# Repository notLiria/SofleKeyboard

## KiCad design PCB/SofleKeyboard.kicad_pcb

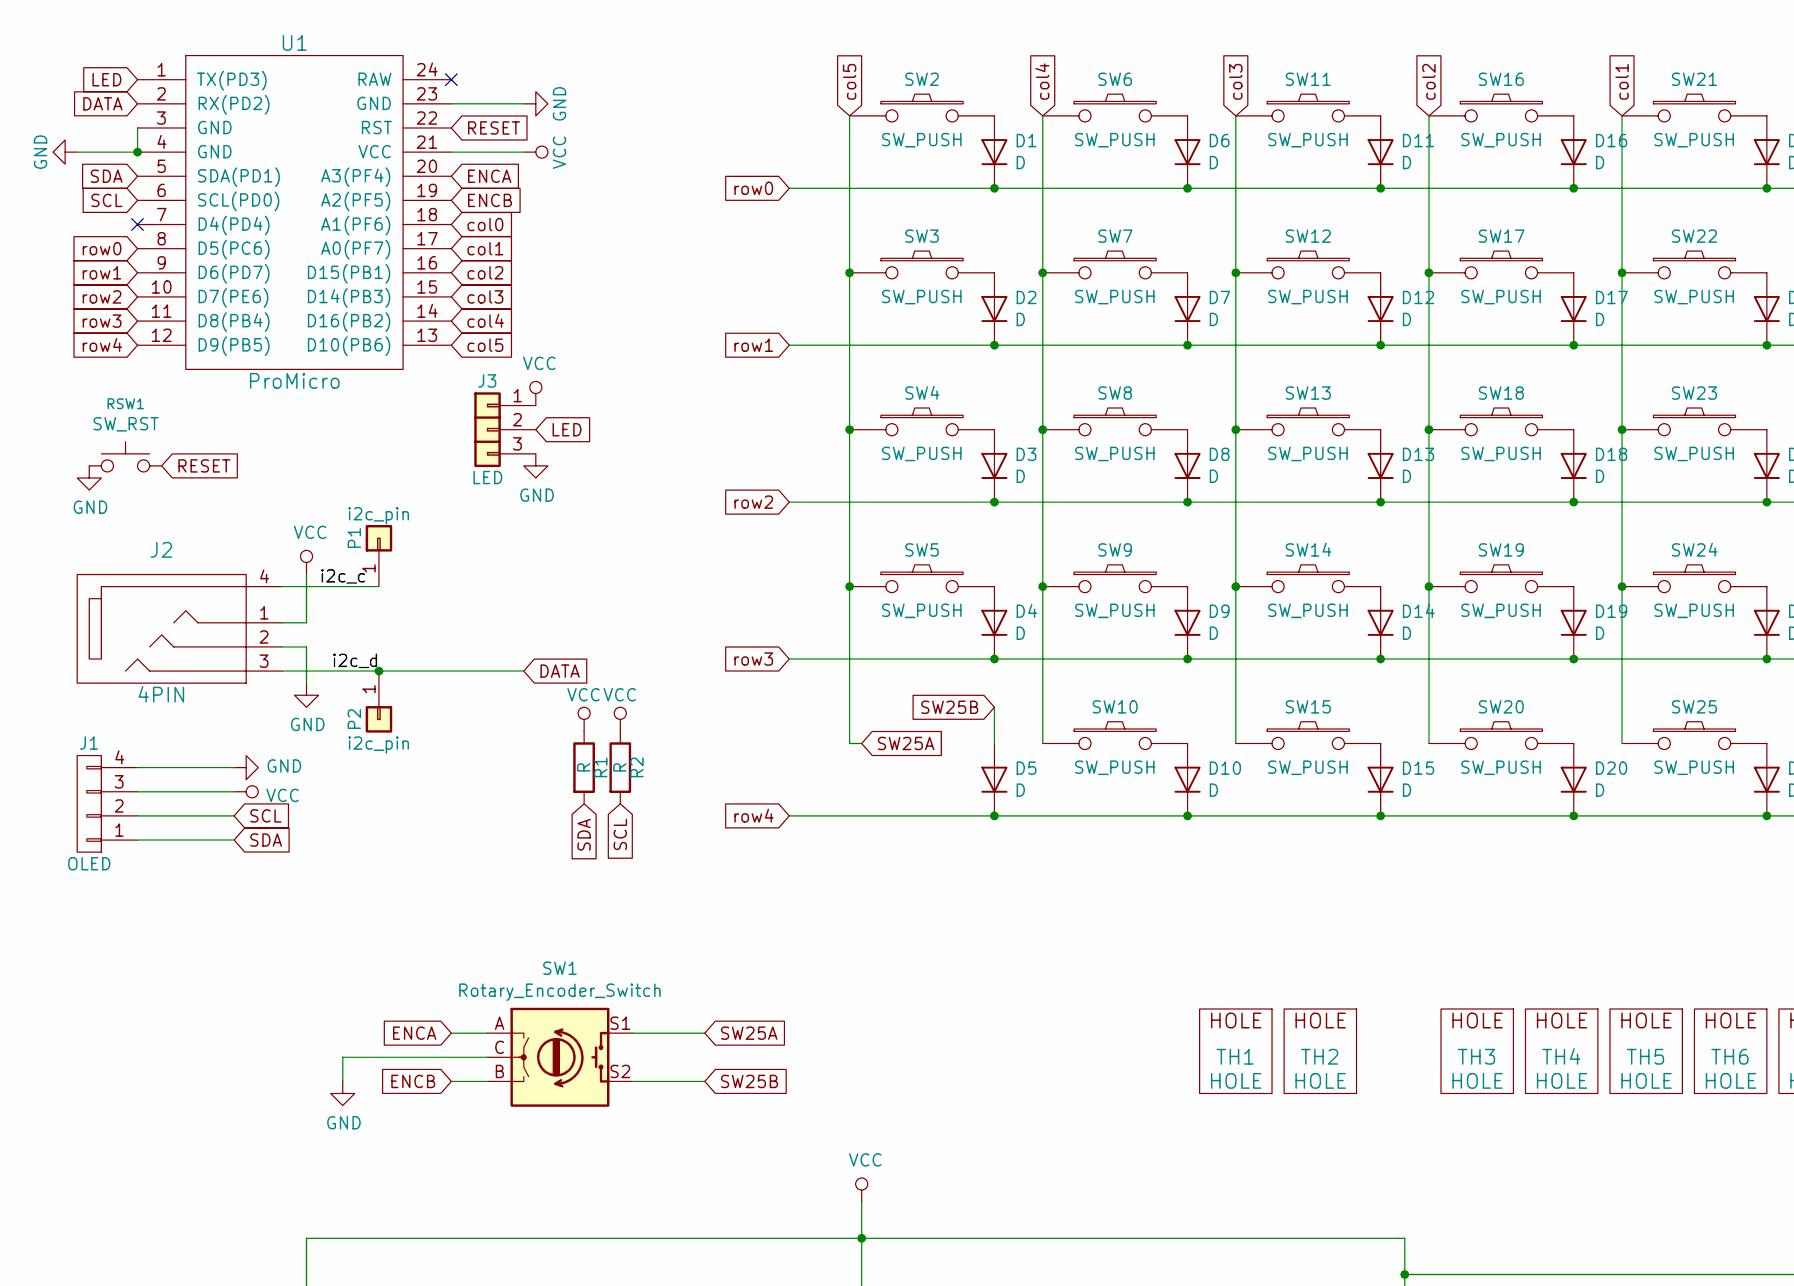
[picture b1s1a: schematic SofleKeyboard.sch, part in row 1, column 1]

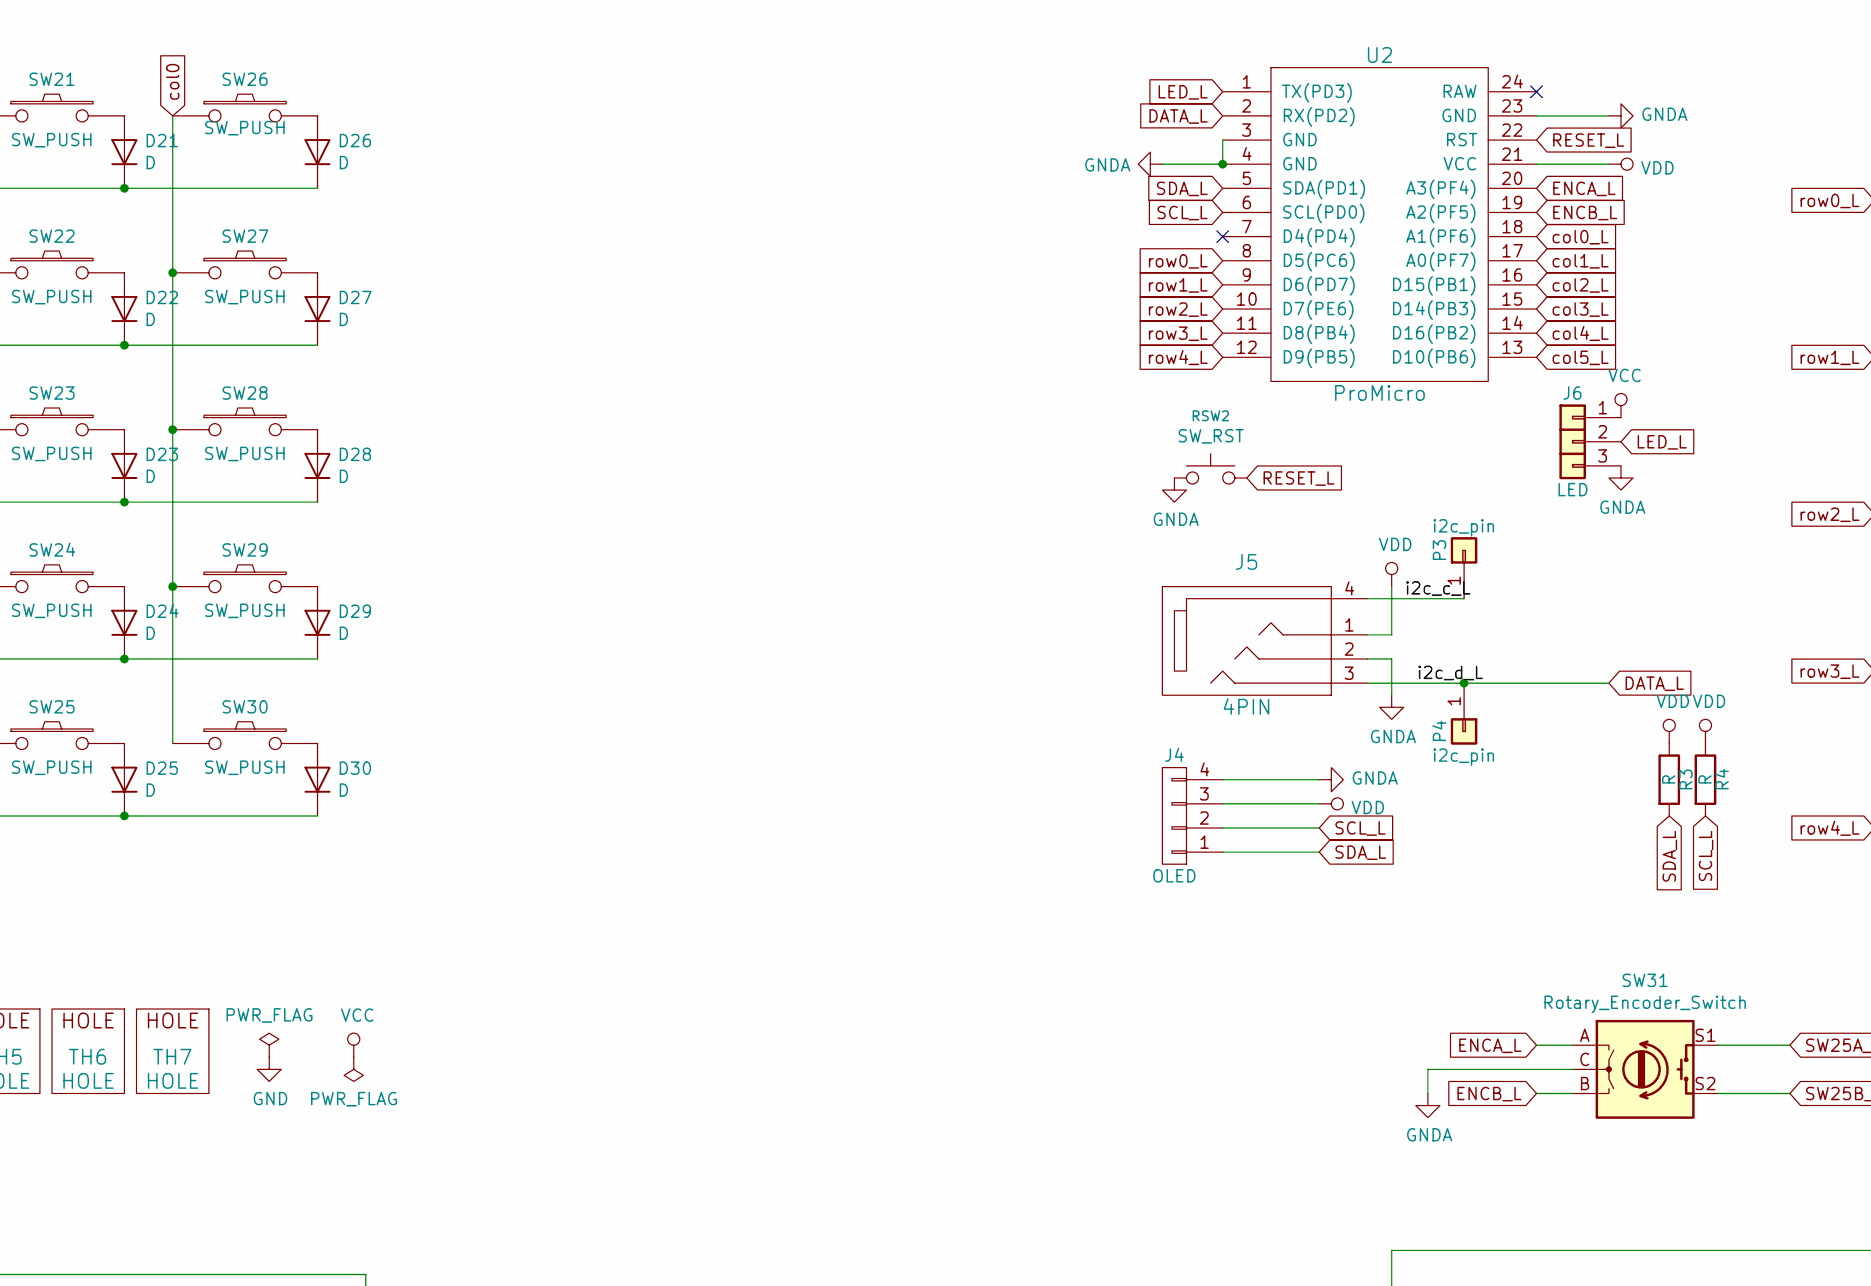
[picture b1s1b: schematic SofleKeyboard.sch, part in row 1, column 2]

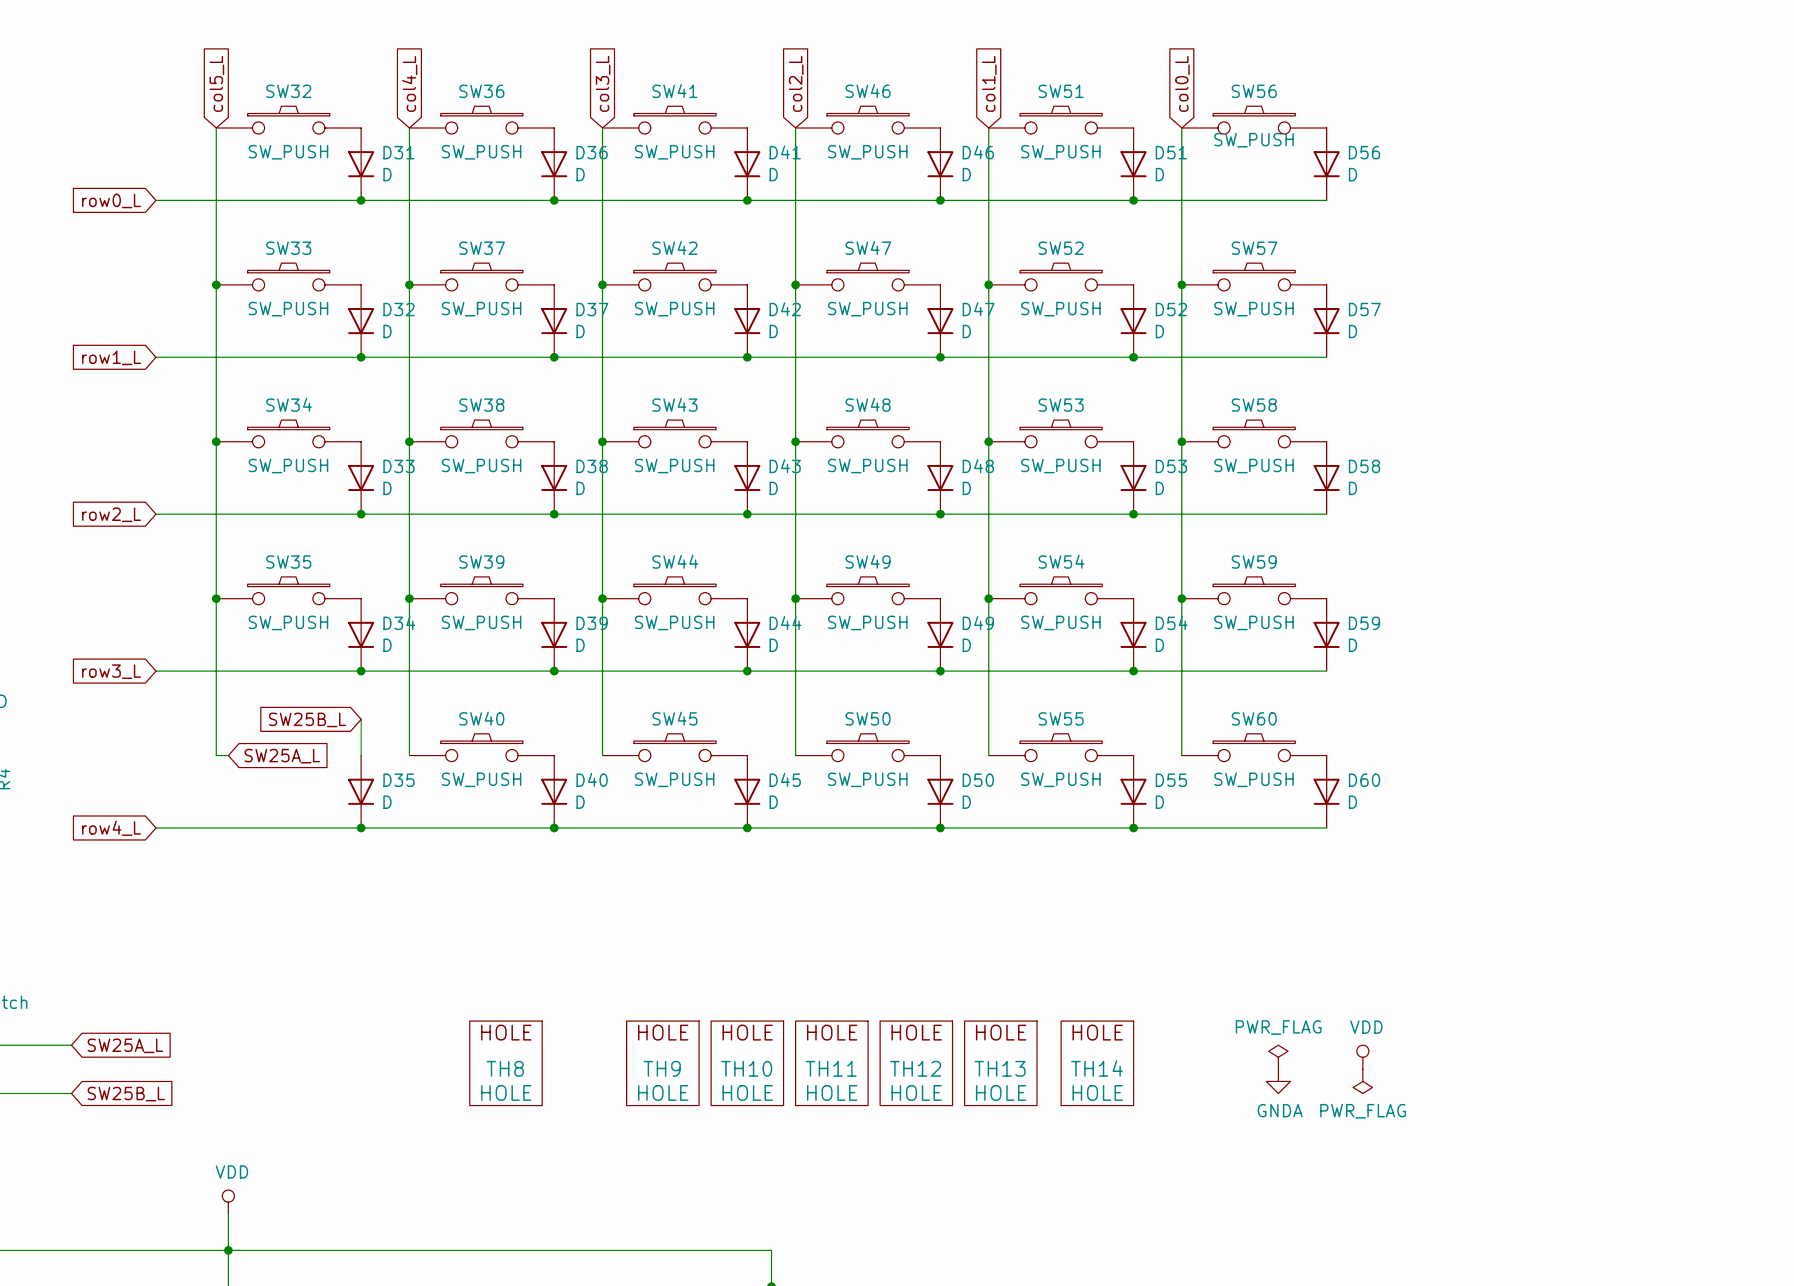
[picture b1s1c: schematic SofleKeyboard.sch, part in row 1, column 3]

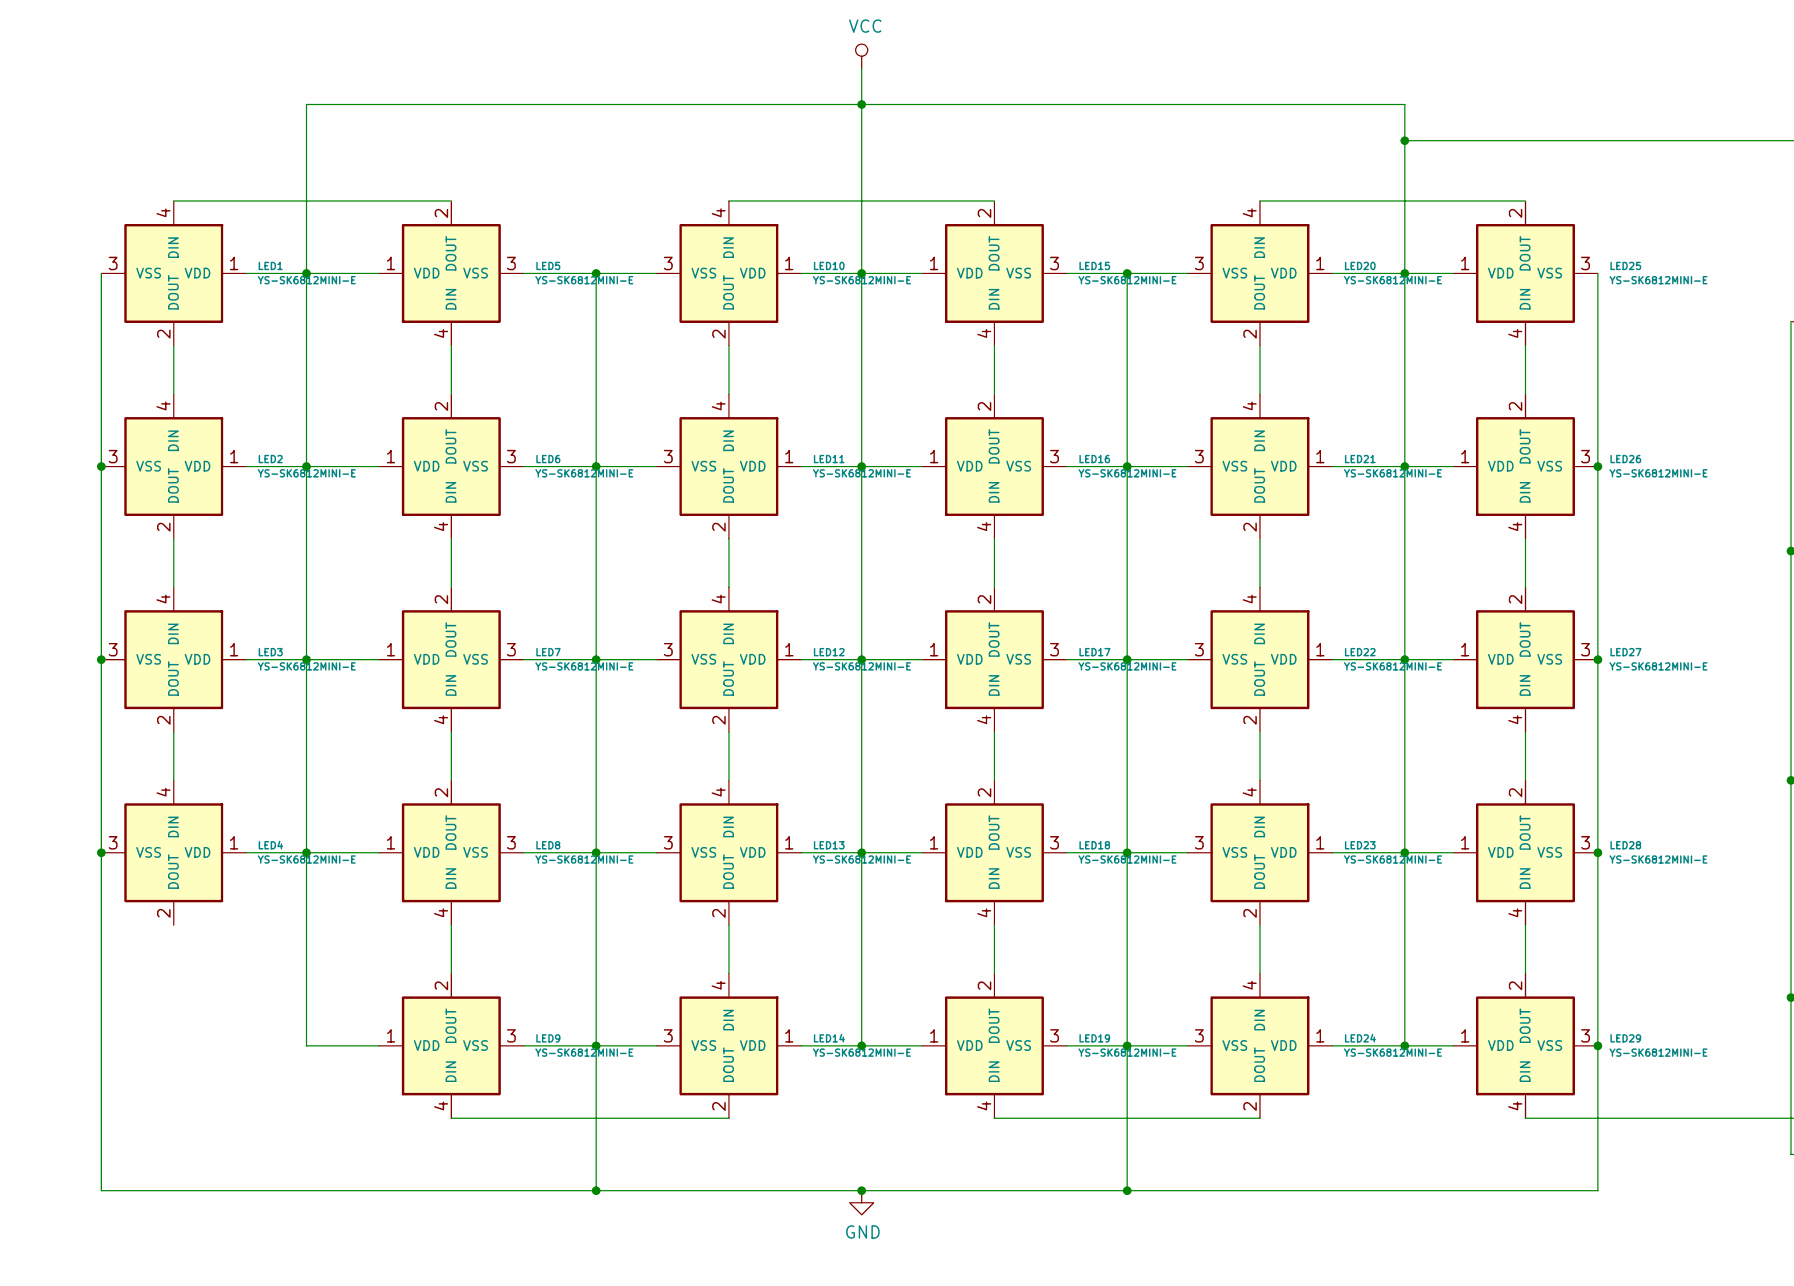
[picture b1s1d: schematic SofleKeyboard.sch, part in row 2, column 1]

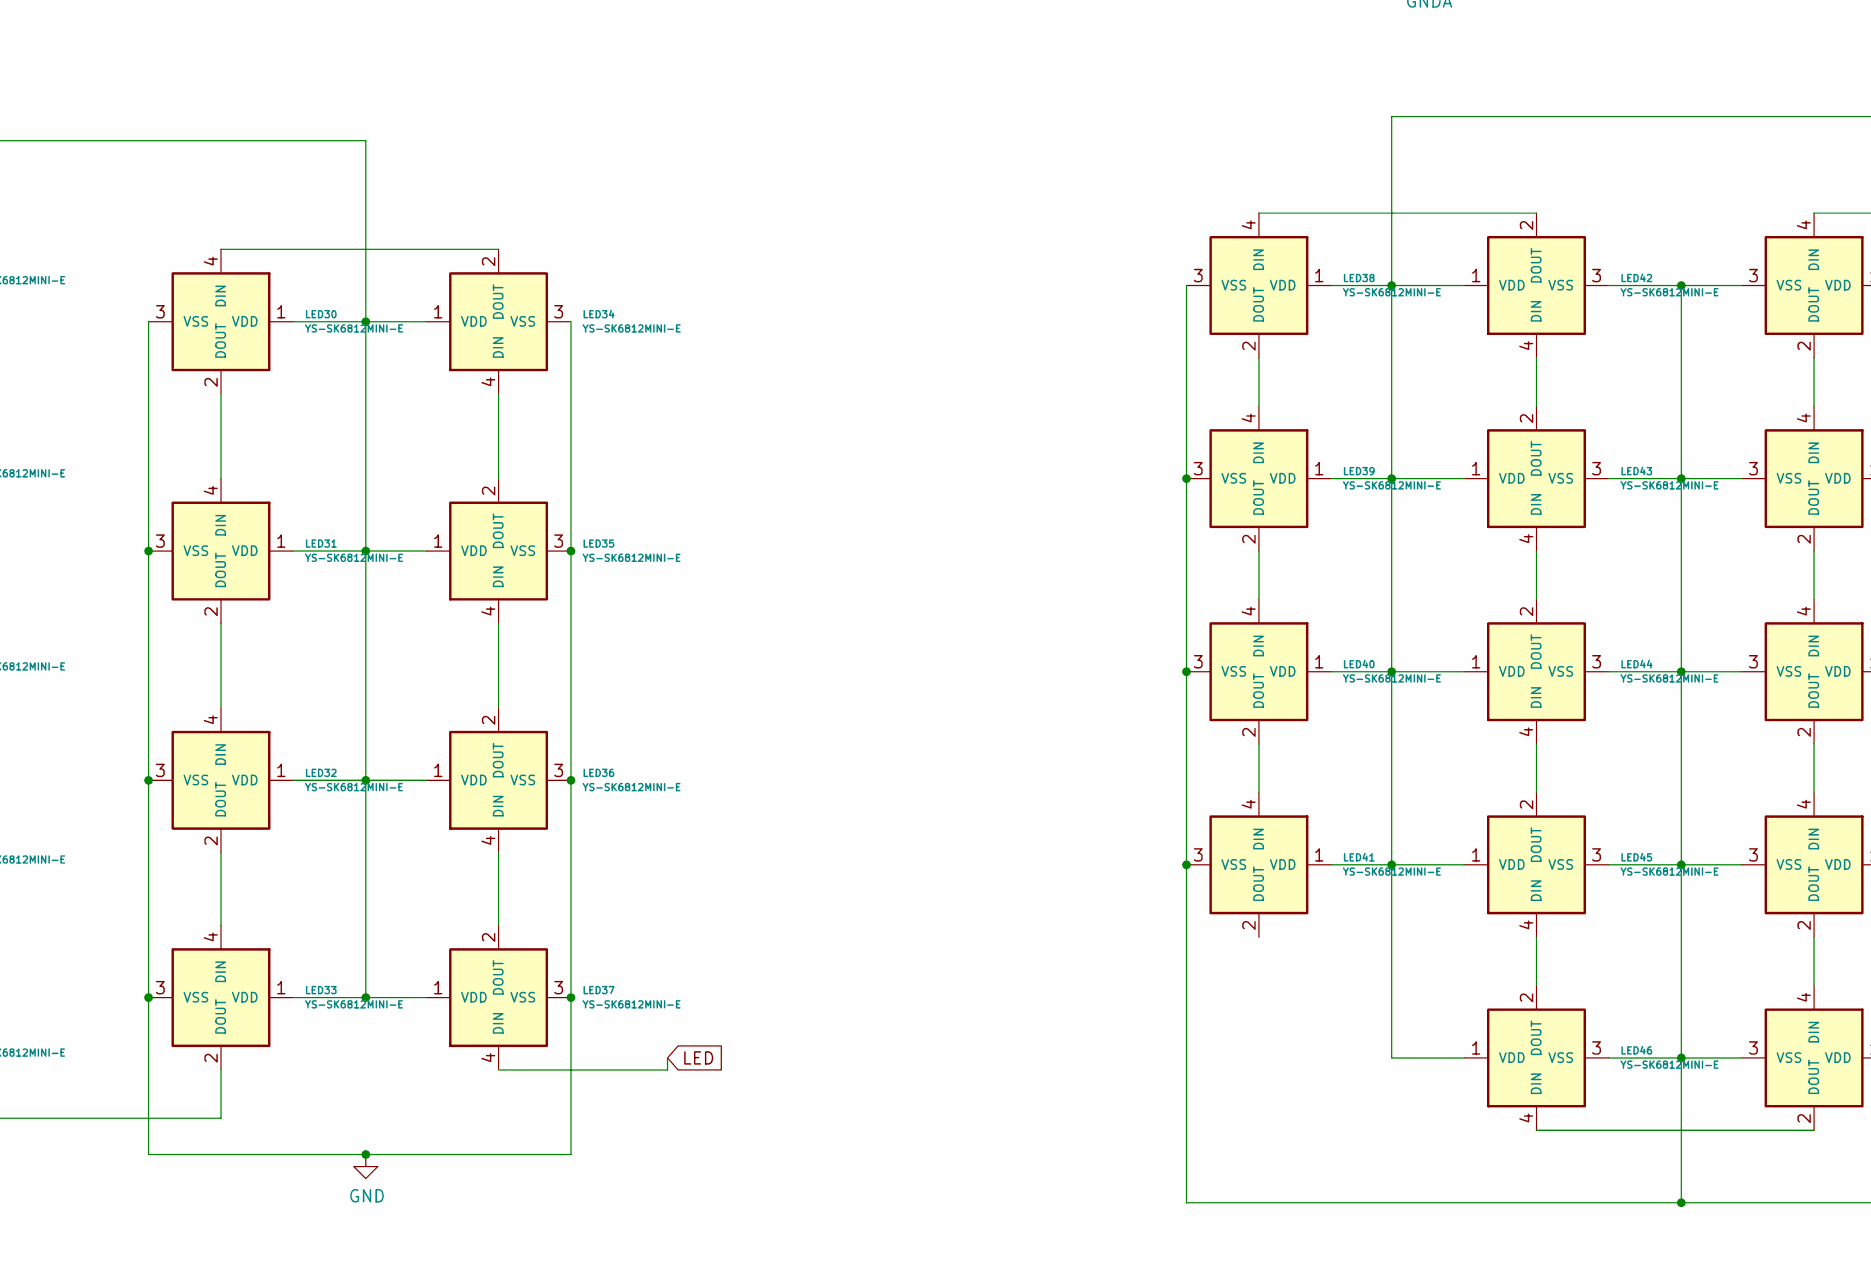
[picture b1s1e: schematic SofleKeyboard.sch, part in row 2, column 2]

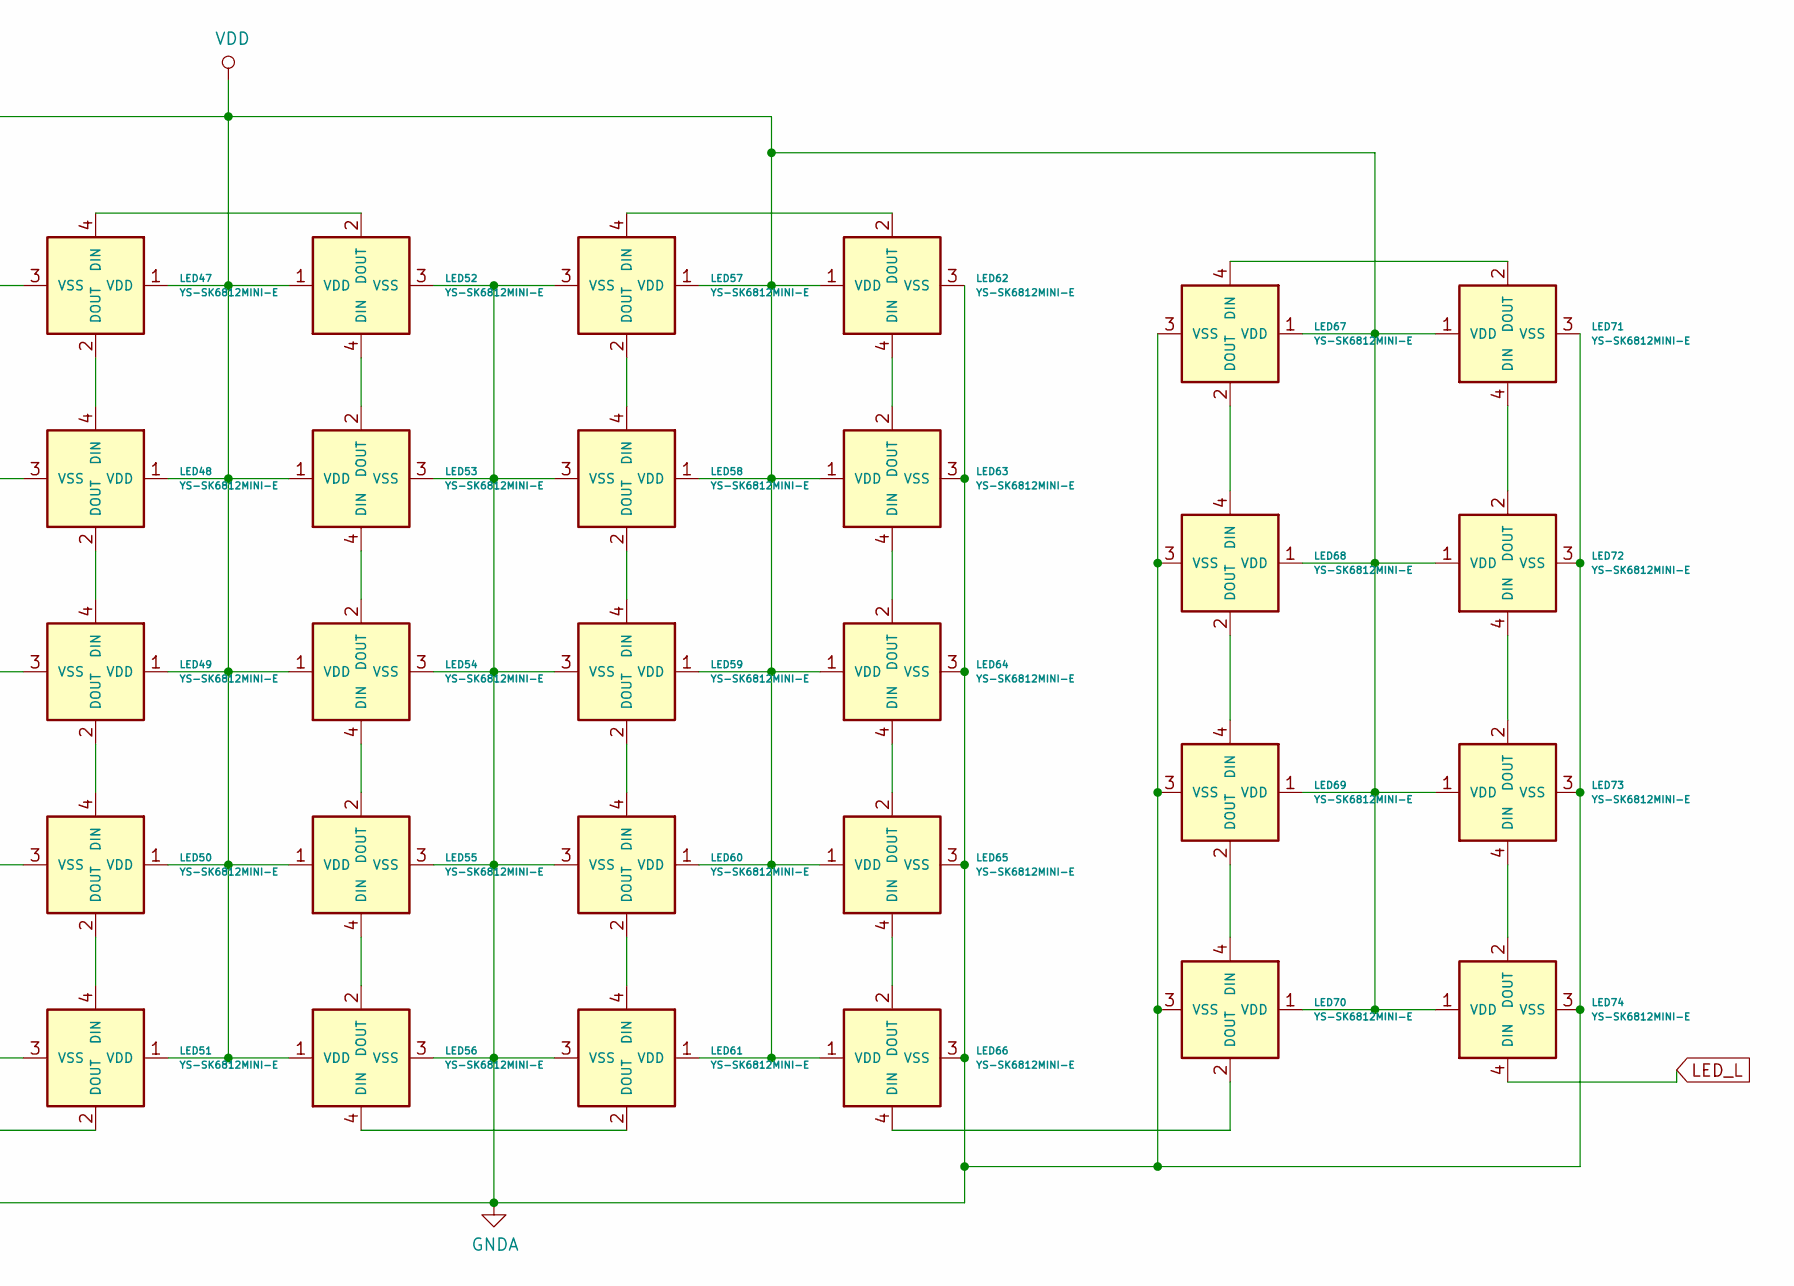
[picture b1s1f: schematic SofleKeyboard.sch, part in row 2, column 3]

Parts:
D1, D2, D3, D4, D5, D6, D7, D8, D9, D10, D11, D12, D13, D14, D15, D16, D17, D18, D19, D20, D21, D22, D23, D24, D25, D26, D27, D28, D29, D30, D31, D32, D33, D34, D35, D36, D37, D38, D39, D40, D41, D42, D43, D44, D45, D46, D47, D48, D49, D50, D51, D52, D53, D54, D55, D56, D57, D58, D59, D60: D; Diode_SOD123
J1, J4: OLED; OLED_4Pin
J2, J5: 4PIN; MJ-4PP-9
J3, J6: LED
LED1, LED2, LED3, LED4, LED5, LED6, LED7, LED8, LED9, LED10, LED11, LED12, LED13, LED14, LED15, LED16, LED17, LED18, LED19, LED20, LED21, LED22, LED23, LED24, LED25, LED26, LED27, LED28, LED29, LED30, LED31, LED32, LED33, LED34, LED35, LED36, LED37, LED38, LED39, LED40, LED41, LED42, LED43, LED44, LED45, LED46, LED47, LED48, LED49, LED50, LED51, LED52, LED53, LED54, LED55, LED56, LED57, LED58, LED59, LED60, LED61, LED62, LED63, LED64, LED65, LED66, LED67, LED68, LED69, LED70, LED71, LED72, LED73, LED74: YS-SK6812MINI-E
P1, P2, P3, P4: i2c_pin; 1pin_conn
R1, R2, R3, R4: R; RESISTOR_mini
RSW1, RSW2: SW_RST; TACT_SWITCH_TVBP06
SW1, SW31: Rotary_Encoder_Switch; RotaryEncoder_Alps_EC11E-Switch_Vertical_H20mm-keebio_modif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
SW2, SW3, SW4, SW5, SW6, SW7, SW8, SW9, SW11, SW12, SW13, SW14, SW15, SW16, SW17, SW18, SW19, SW20, SW21, SW22, SW23, SW24, SW25, SW26, SW27, SW28, SW29, SW30, SW32, SW33, SW34, SW35, SW36, SW37, SW38, SW39, SW41, SW42, SW43, SW44, SW45, SW46, SW47, SW48, SW49, SW50, SW51, SW52, SW53, SW54, SW55, SW56, SW57, SW58, SW59, SW60: SW_PUSH; CherryMX_KailhLowProfile_Hotswap
SW10, SW40: SW_PUSH; CherryMX_KailhLowProfile_Hotswap_1.5
TH1, TH2, TH8: HOLE; M2_HOLE_PCB
TH3, TH4, TH5, TH6, TH7, TH9, TH10, TH11, TH12, TH13, TH14: HOLE; HOLE_M2_TH
U1, U2: ProMicro

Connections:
/i2c_c: J2.4, P1.1
/i2c_c_L: J5.4, P3.1
DATA: J2.3, P2.1, U1.2 (RX(PD2)); also elsewhere on the board
DATA_L: J5.3, P4.1, U2.2 (RX(PD2))
ENCA: SW1.A, U1.20 (A3(PF4))
ENCA_L: SW31.A, U2.20 (A3(PF4))
ENCB: SW1.B, U1.19 (A2(PF5))
ENCB_L: SW31.B, U2.19 (A2(PF5))
GND: J1.4, J2.2, J3.3, LED1.3 (VSS), LED2.3 (VSS), LED3.3 (VSS), LED4.3 (VSS), LED5.3 (VSS), LED6.3 (VSS), LED7.3 (VSS), LED8.3 (VSS), LED9.3 (VSS), LED10.3 (VSS), LED11.3 (VSS), LED12.3 (VSS), LED13.3 (VSS), LED14.3 (VSS), LED15.3 (VSS), LED16.3 (VSS), LED17.3 (VSS), LED18.3 (VSS), LED19.3 (VSS), LED20.3 (VSS), LED21.3 (VSS), LED22.3 (VSS), LED23.3 (VSS), LED24.3 (VSS), LED25.3 (VSS), LED26.3 (VSS), LED27.3 (VSS), LED28.3 (VSS), LED29.3 (VSS), LED30.3 (VSS), LED31.3 (VSS), LED32.3 (VSS), LED33.3 (VSS), LED34.3 (VSS), LED35.3 (VSS), LED36.3 (VSS), LED37.3 (VSS), RSW1.1, SW1.C, U1.3 (GND), U1.4 (GND), U1.23 (GND)
GNDA: J4.4, J5.2, J6.3, LED38.3 (VSS), LED39.3 (VSS), LED40.3 (VSS), LED41.3 (VSS), LED42.3 (VSS), LED43.3 (VSS), LED44.3 (VSS), LED45.3 (VSS), LED46.3 (VSS), LED47.3 (VSS), LED48.3 (VSS), LED49.3 (VSS), LED50.3 (VSS), LED51.3 (VSS), LED52.3 (VSS), LED53.3 (VSS), LED54.3 (VSS), LED55.3 (VSS), LED56.3 (VSS), LED57.3 (VSS), LED58.3 (VSS), LED59.3 (VSS), LED60.3 (VSS), LED61.3 (VSS), LED62.3 (VSS), LED63.3 (VSS), LED64.3 (VSS), LED65.3 (VSS), LED66.3 (VSS), LED67.3 (VSS), LED68.3 (VSS), LED69.3 (VSS), LED70.3 (VSS), LED71.3 (VSS), LED72.3 (VSS), LED73.3 (VSS), LED74.3 (VSS), RSW2.1, SW31.C, U2.3 (GND), U2.4 (GND), U2.23 (GND)
LED: J3.2, LED37.4 (DIN), U1.1 (TX(PD3))
LED_L: J6.2, LED74.4 (DIN), U2.1 (TX(PD3))
unnamed: D1.2 (A), SW2.2
unnamed: D2.2 (A), SW3.2
unnamed: D3.2 (A), SW4.2
unnamed: D4.2 (A), SW5.2
unnamed: D6.2 (A), SW6.2
unnamed: D7.2 (A), SW7.2
unnamed: D8.2 (A), SW8.2
unnamed: D9.2 (A), SW9.2
unnamed: D10.2 (A), SW10.2
unnamed: D11.2 (A), SW11.2
unnamed: D12.2 (A), SW12.2
unnamed: D13.2 (A), SW13.2
unnamed: D14.2 (A), SW14.2
unnamed: D15.2 (A), SW15.2
unnamed: D16.2 (A), SW16.2
unnamed: D17.2 (A), SW17.2
unnamed: D18.2 (A), SW18.2
unnamed: D19.2 (A), SW19.2
unnamed: D20.2 (A), SW20.2
unnamed: D21.2 (A), SW21.2
unnamed: D22.2 (A), SW22.2
unnamed: D23.2 (A), SW23.2
unnamed: D24.2 (A), SW24.2
unnamed: D25.2 (A), SW25.2
unnamed: D26.2 (A), SW26.2
unnamed: D27.2 (A), SW27.2
unnamed: D28.2 (A), SW28.2
unnamed: D29.2 (A), SW29.2
unnamed: D30.2 (A), SW30.2
unnamed: D31.2 (A), SW32.2
unnamed: D32.2 (A), SW33.2
unnamed: D33.2 (A), SW34.2
unnamed: D34.2 (A), SW35.2
unnamed: D36.2 (A), SW36.2
unnamed: D37.2 (A), SW37.2
unnamed: D38.2 (A), SW38.2
unnamed: D39.2 (A), SW39.2
unnamed: D40.2 (A), SW40.2
unnamed: D41.2 (A), SW41.2
unnamed: D42.2 (A), SW42.2
unnamed: D43.2 (A), SW43.2
unnamed: D44.2 (A), SW44.2
unnamed: D45.2 (A), SW45.2
unnamed: D46.2 (A), SW46.2
unnamed: D47.2 (A), SW47.2
unnamed: D48.2 (A), SW48.2
unnamed: D49.2 (A), SW49.2
unnamed: D50.2 (A), SW50.2
unnamed: D51.2 (A), SW51.2
unnamed: D52.2 (A), SW52.2
unnamed: D53.2 (A), SW53.2
unnamed: D54.2 (A), SW54.2
unnamed: D55.2 (A), SW55.2
unnamed: D56.2 (A), SW56.2
unnamed: D57.2 (A), SW57.2
unnamed: D58.2 (A), SW58.2
unnamed: D59.2 (A), SW59.2
unnamed: D60.2 (A), SW60.2
unnamed: LED1.2 (DOUT), LED2.4 (DIN)
unnamed: LED1.4 (DIN), LED5.2 (DOUT)
unnamed: LED2.2 (DOUT), LED3.4 (DIN)
unnamed: LED3.2 (DOUT), LED4.4 (DIN)
unnamed: LED5.4 (DIN), LED6.2 (DOUT)
unnamed: LED6.4 (DIN), LED7.2 (DOUT)
unnamed: LED7.4 (DIN), LED8.2 (DOUT)
unnamed: LED8.4 (DIN), LED9.2 (DOUT)
unnamed: LED10.2 (DOUT), LED11.4 (DIN)
unnamed: LED10.4 (DIN), LED15.2 (DOUT)
unnamed: LED11.2 (DOUT), LED12.4 (DIN)
unnamed: LED12.2 (DOUT), LED13.4 (DIN)
unnamed: LED13.2 (DOUT), LED14.4 (DIN)
unnamed: LED9.4 (DIN), LED14.2 (DOUT)
unnamed: LED15.4 (DIN), LED16.2 (DOUT)
unnamed: LED16.4 (DIN), LED17.2 (DOUT)
unnamed: LED17.4 (DIN), LED18.2 (DOUT)
unnamed: LED18.4 (DIN), LED19.2 (DOUT)
unnamed: LED19.4 (DIN), LED24.2 (DOUT)
unnamed: LED20.2 (DOUT), LED21.4 (DIN)
unnamed: LED20.4 (DIN), LED25.2 (DOUT)
unnamed: LED21.2 (DOUT), LED22.4 (DIN)
unnamed: LED22.2 (DOUT), LED23.4 (DIN)
unnamed: LED23.2 (DOUT), LED24.4 (DIN)
unnamed: LED25.4 (DIN), LED26.2 (DOUT)
unnamed: LED26.4 (DIN), LED27.2 (DOUT)
unnamed: LED27.4 (DIN), LED28.2 (DOUT)
unnamed: LED28.4 (DIN), LED29.2 (DOUT)
unnamed: LED29.4 (DIN), LED33.2 (DOUT)
unnamed: LED30.2 (DOUT), LED31.4 (DIN)
unnamed: LED30.4 (DIN), LED34.2 (DOUT)
unnamed: LED31.2 (DOUT), LED32.4 (DIN)
unnamed: LED32.2 (DOUT), LED33.4 (DIN)
unnamed: LED34.4 (DIN), LED35.2 (DOUT)
unnamed: LED35.4 (DIN), LED36.2 (DOUT)
unnamed: LED36.4 (DIN), LED37.2 (DOUT)
unnamed: LED38.2 (DOUT), LED39.4 (DIN)
unnamed: LED38.4 (DIN), LED42.2 (DOUT)
unnamed: LED39.2 (DOUT), LED40.4 (DIN)
unnamed: LED40.2 (DOUT), LED41.4 (DIN)
unnamed: LED42.4 (DIN), LED43.2 (DOUT)
unnamed: LED43.4 (DIN), LED44.2 (DOUT)
unnamed: LED44.4 (DIN), LED45.2 (DOUT)
unnamed: LED45.4 (DIN), LED46.2 (DOUT)
unnamed: LED46.4 (DIN), LED51.2 (DOUT)
unnamed: LED47.2 (DOUT), LED48.4 (DIN)
unnamed: LED47.4 (DIN), LED52.2 (DOUT)
unnamed: LED48.2 (DOUT), LED49.4 (DIN)
unnamed: LED49.2 (DOUT), LED50.4 (DIN)
unnamed: LED50.2 (DOUT), LED51.4 (DIN)
unnamed: LED52.4 (DIN), LED53.2 (DOUT)
unnamed: LED53.4 (DIN), LED54.2 (DOUT)
unnamed: LED54.4 (DIN), LED55.2 (DOUT)
unnamed: LED55.4 (DIN), LED56.2 (DOUT)
unnamed: LED56.4 (DIN), LED61.2 (DOUT)
unnamed: LED57.2 (DOUT), LED58.4 (DIN)
unnamed: LED57.4 (DIN), LED62.2 (DOUT)
unnamed: LED58.2 (DOUT), LED59.4 (DIN)
unnamed: LED59.2 (DOUT), LED60.4 (DIN)
unnamed: LED60.2 (DOUT), LED61.4 (DIN)
unnamed: LED62.4 (DIN), LED63.2 (DOUT)
unnamed: LED63.4 (DIN), LED64.2 (DOUT)
unnamed: LED64.4 (DIN), LED65.2 (DOUT)
unnamed: LED65.4 (DIN), LED66.2 (DOUT)
unnamed: LED66.4 (DIN), LED70.2 (DOUT)
unnamed: LED67.2 (DOUT), LED68.4 (DIN)
unnamed: LED67.4 (DIN), LED71.2 (DOUT)
unnamed: LED68.2 (DOUT), LED69.4 (DIN)
unnamed: LED69.2 (DOUT), LED70.4 (DIN)
unnamed: LED71.4 (DIN), LED72.2 (DOUT)
unnamed: LED72.4 (DIN), LED73.2 (DOUT)
unnamed: LED73.4 (DIN), LED74.2 (DOUT)
RESET: RSW1.2, U1.22 (RST)
RESET_L: RSW2.2, U2.22 (RST)
SCL: J1.2, R2.2, U1.6 (SCL(PD0))
SCL_L: J4.2, R4.2, U2.6 (SCL(PD0))
SDA: J1.1, R1.2, U1.5 (SDA(PD1))
SDA_L: J4.1, R3.2, U2.5 (SDA(PD1))
SW25A: SW1.S1, SW2.1, SW3.1, SW4.1, SW5.1, U1.13 (D10(PB6))
SW25A_L: SW31.S1, SW32.1, SW33.1, SW34.1, SW35.1, U2.13 (D10(PB6))
SW25B: D5.2 (A), SW1.S2
SW25B_L: D35.2 (A), SW31.S2
VCC: J1.3, J2.1, J3.1, J6.1, LED1.1 (VDD), LED2.1 (VDD), LED3.1 (VDD), LED4.1 (VDD), LED5.1 (VDD), LED6.1 (VDD), LED7.1 (VDD), LED8.1 (VDD), LED9.1 (VDD), LED10.1 (VDD), LED11.1 (VDD), LED12.1 (VDD), LED13.1 (VDD), LED14.1 (VDD), LED15.1 (VDD), LED16.1 (VDD), LED17.1 (VDD), LED18.1 (VDD), LED19.1 (VDD), LED20.1 (VDD), LED21.1 (VDD), LED22.1 (VDD), LED23.1 (VDD), LED24.1 (VDD), LED25.1 (VDD), LED26.1 (VDD), LED27.1 (VDD), LED28.1 (VDD), LED29.1 (VDD), LED30.1 (VDD), LED31.1 (VDD), LED32.1 (VDD), LED33.1 (VDD), LED34.1 (VDD), LED35.1 (VDD), LED36.1 (VDD), LED37.1 (VDD), R1.1, R2.1, U1.21 (VCC)
VDD: J4.3, J5.1, LED38.1 (VDD), LED39.1 (VDD), LED40.1 (VDD), LED41.1 (VDD), LED42.1 (VDD), LED43.1 (VDD), LED44.1 (VDD), LED45.1 (VDD), LED46.1 (VDD), LED47.1 (VDD), LED48.1 (VDD), LED49.1 (VDD), LED50.1 (VDD), LED51.1 (VDD), LED52.1 (VDD), LED53.1 (VDD), LED54.1 (VDD), LED55.1 (VDD), LED56.1 (VDD), LED57.1 (VDD), LED58.1 (VDD), LED59.1 (VDD), LED60.1 (VDD), LED61.1 (VDD), LED62.1 (VDD), LED63.1 (VDD), LED64.1 (VDD), LED65.1 (VDD), LED66.1 (VDD), LED67.1 (VDD), LED68.1 (VDD), LED69.1 (VDD), LED70.1 (VDD), LED71.1 (VDD), LED72.1 (VDD), LED73.1 (VDD), LED74.1 (VDD), R3.1, R4.1, U2.21 (VCC)
col0: SW26.1, SW27.1, SW28.1, SW29.1, SW30.1, U1.18 (A1(PF6))
col0_L: SW56.1, SW57.1, SW58.1, SW59.1, SW60.1, U2.18 (A1(PF6))
col1: SW21.1, SW22.1, SW23.1, SW24.1, SW25.1, U1.17 (A0(PF7))
col1_L: SW51.1, SW52.1, SW53.1, SW54.1, SW55.1, U2.17 (A0(PF7))
col2: SW16.1, SW17.1, SW18.1, SW19.1, SW20.1, U1.16 (D15(PB1))
col2_L: SW46.1, SW47.1, SW48.1, SW49.1, SW50.1, U2.16 (D15(PB1))
col3: SW11.1, SW12.1, SW13.1, SW14.1, SW15.1, U1.15 (D14(PB3))
col3_L: SW41.1, SW42.1, SW43.1, SW44.1, SW45.1, U2.15 (D14(PB3))
col4: SW6.1, SW7.1, SW8.1, SW9.1, SW10.1, U1.14 (D16(PB2))
col4_L: SW36.1, SW37.1, SW38.1, SW39.1, SW40.1, U2.14 (D16(PB2))
row0: D1.1 (K), D6.1 (K), D11.1 (K), D16.1 (K), D21.1 (K), D26.1 (K), U1.8 (D5(PC6))
row0_L: D31.1 (K), D36.1 (K), D41.1 (K), D46.1 (K), D51.1 (K), D56.1 (K), U2.8 (D5(PC6))
row1: D2.1 (K), D7.1 (K), D12.1 (K), D17.1 (K), D22.1 (K), D27.1 (K), U1.9 (D6(PD7))
row1_L: D32.1 (K), D37.1 (K), D42.1 (K), D47.1 (K), D52.1 (K), D57.1 (K), U2.9 (D6(PD7))
row2: D3.1 (K), D8.1 (K), D13.1 (K), D18.1 (K), D23.1 (K), D28.1 (K), U1.10 (D7(PE6))
row2_L: D33.1 (K), D38.1 (K), D43.1 (K), D48.1 (K), D53.1 (K), D58.1 (K), U2.10 (D7(PE6))
row3: D4.1 (K), D9.1 (K), D14.1 (K), D19.1 (K), D24.1 (K), D29.1 (K), U1.11 (D8(PB4))
row3_L: D34.1 (K), D39.1 (K), D44.1 (K), D49.1 (K), D54.1 (K), D59.1 (K), U2.11 (D8(PB4))
row4: D5.1 (K), D10.1 (K), D15.1 (K), D20.1 (K), D25.1 (K), D30.1 (K), U1.12 (D9(PB5))
row4_L: D35.1 (K), D40.1 (K), D45.1 (K), D50.1 (K), D55.1 (K), D60.1 (K), U2.12 (D9(PB5))

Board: 2 copper layers, 227 parts (97 on the bottom side), 174 nets, no tracks yet.

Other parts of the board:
W1: jumper; jumper_data

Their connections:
DATA: W1.1; also elsewhere on the board

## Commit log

2020-10-03 Added CRKBDv3 style SK6812-E LEDs and panelization
2020-10-04 Cleaned up stray edges in pcb
2020-10-04 Panelized PCB
